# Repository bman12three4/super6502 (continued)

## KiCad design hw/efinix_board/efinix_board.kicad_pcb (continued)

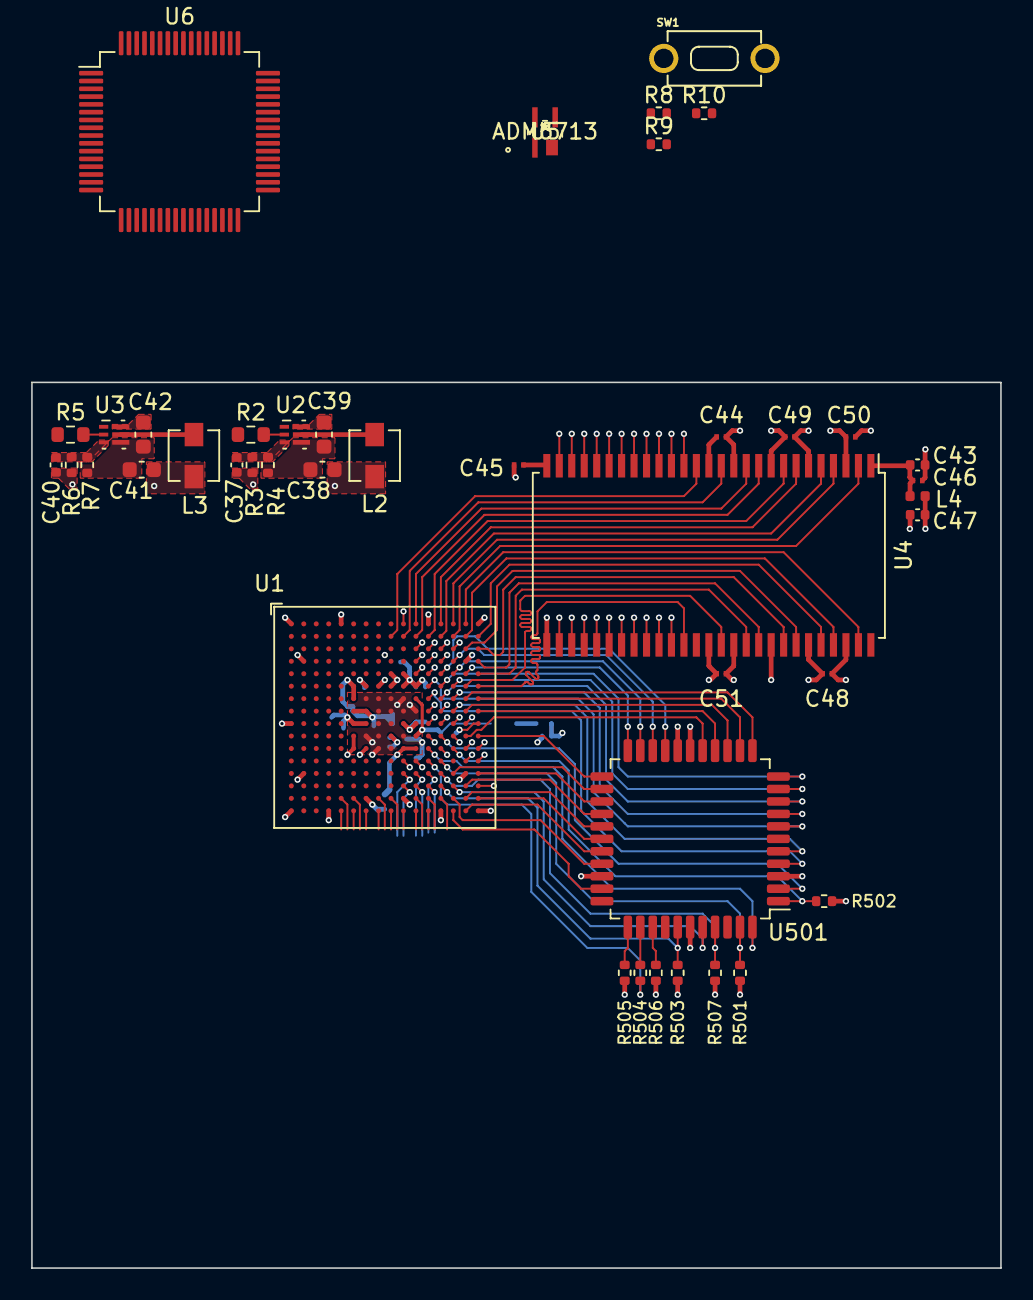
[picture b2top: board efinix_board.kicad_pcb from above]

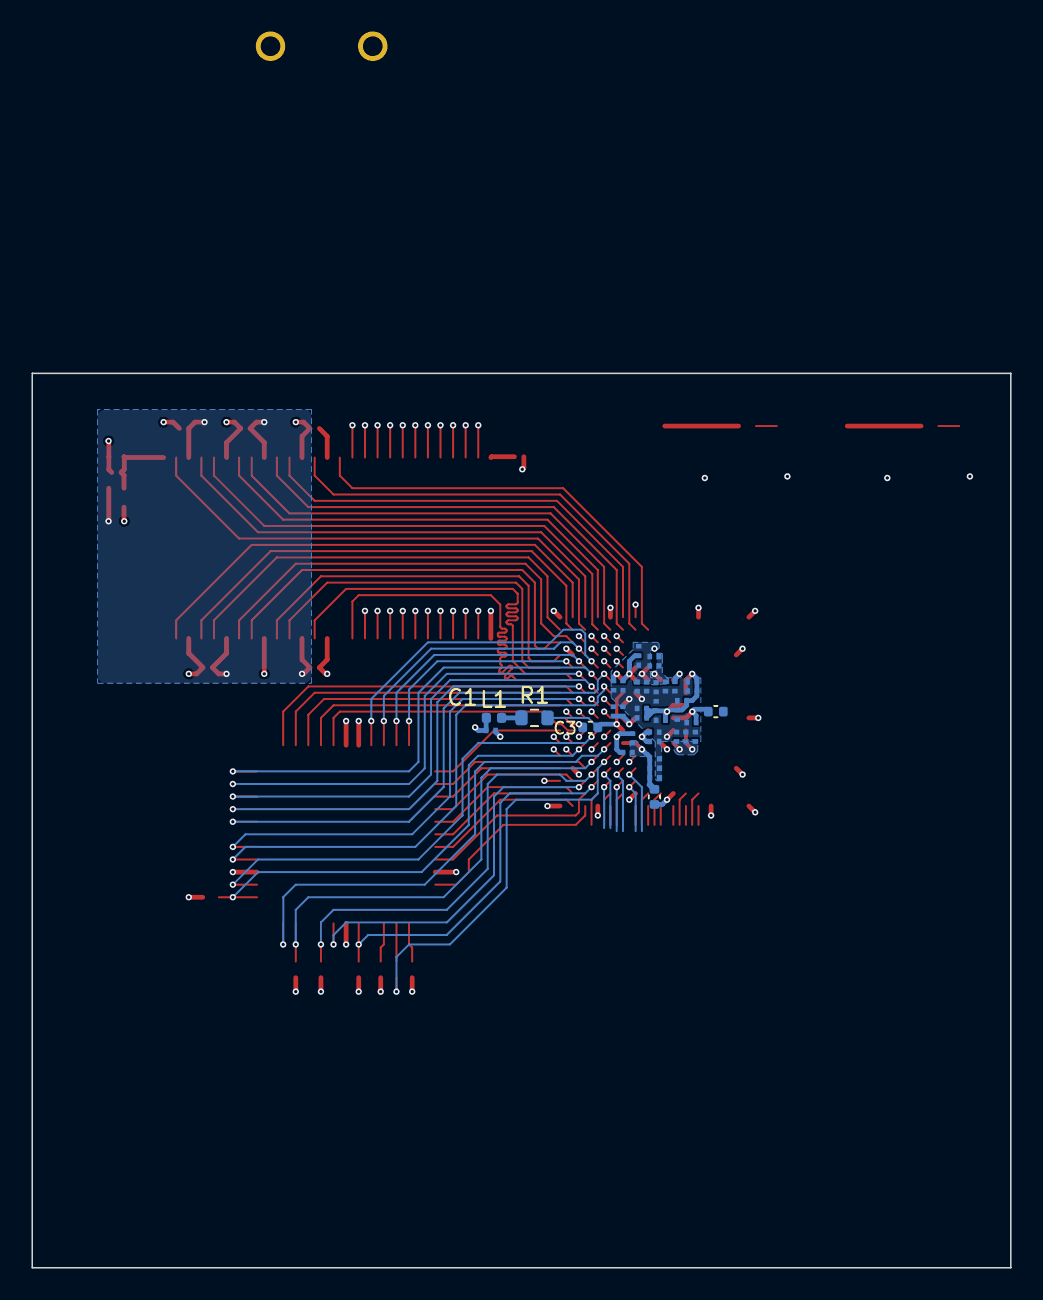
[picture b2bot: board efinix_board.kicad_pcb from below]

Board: 6 copper layers, 62.2 x 56.9 mm, 80 parts (38 on the bottom side), 92 nets.

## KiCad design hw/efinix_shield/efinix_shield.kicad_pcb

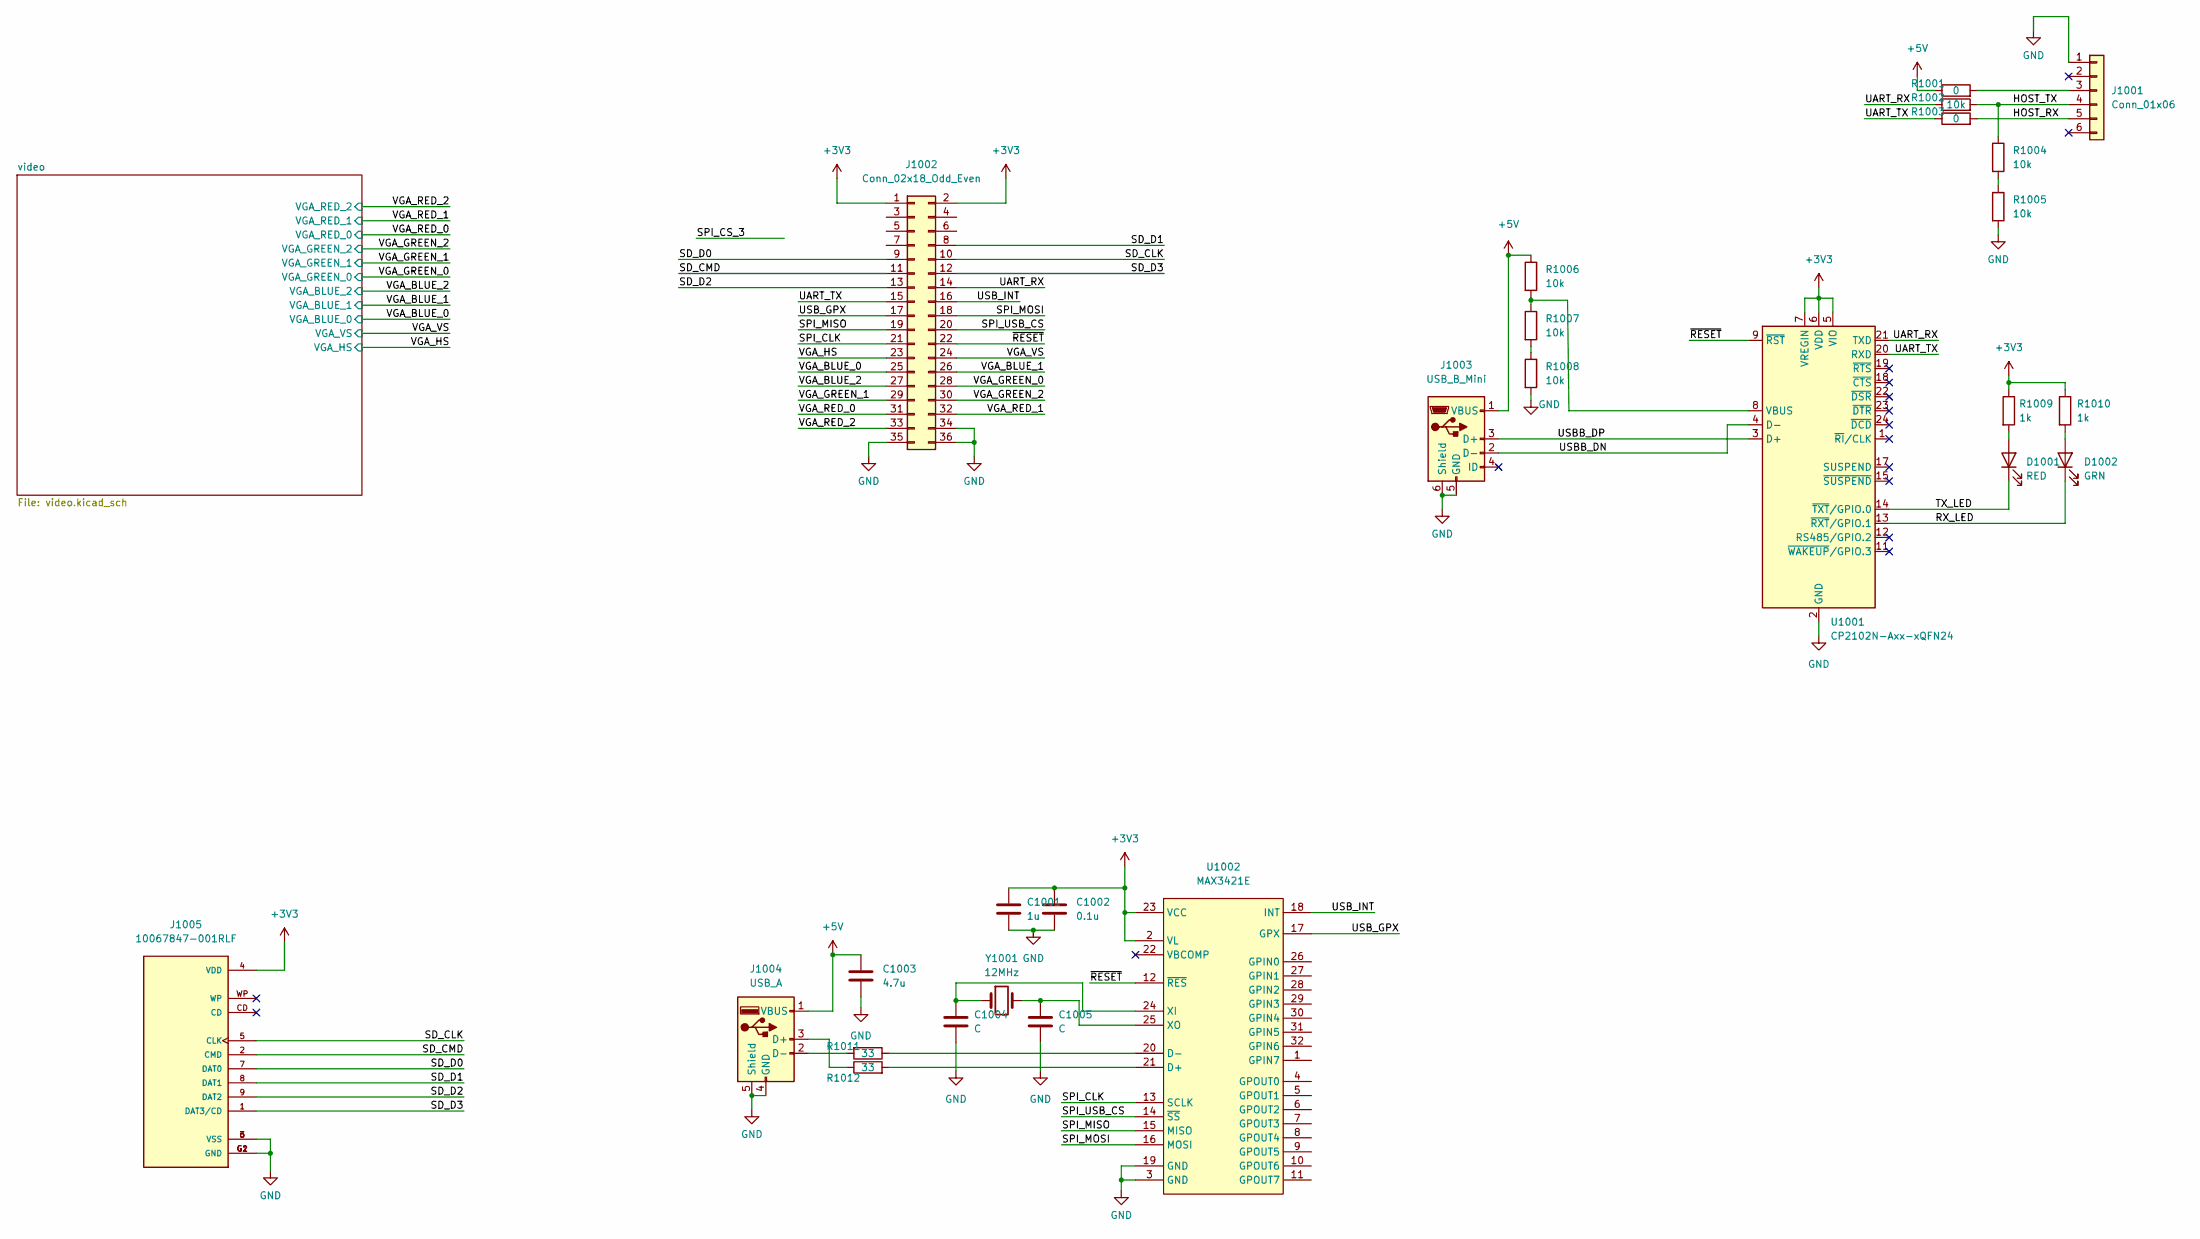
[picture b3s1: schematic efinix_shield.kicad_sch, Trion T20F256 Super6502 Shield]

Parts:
C1001: 1u; C_0805_2012Metric_Pad1.18x1.45mm_HandSolder
C1002: 0.1u; C_0805_2012Metric_Pad1.18x1.45mm_HandSolder
C1003: 4.7u; C_0805_2012Metric_Pad1.18x1.45mm_HandSolder
C1004, C1005: C; C_0805_2012Metric_Pad1.18x1.45mm_HandSolder
D1001: RED; LED_0805_2012Metric_Pad1.15x1.40mm_HandSolder
D1002: GRN; LED_0805_2012Metric_Pad1.15x1.40mm_HandSolder
J1001: Conn_01x06; PinHeader_1x06_P2.54mm_Vertical
J1002: Conn_02x18_Odd_Even; PinSocket_2x18_P2.54mm_Vertical
J1003: USB_B_Mini; USB_Mini-B_Wuerth_65100516121_Horizontal
J1004: USB_A; FCI_87520-0010BLF
J1005: 10067847-001RLF; AMPHENOL_10067847-001RLF; PARTREV K
R1001, R1003: 0; R_0805_2012Metric_Pad1.20x1.40mm_HandSolder
R1002, R1004, R1005, R1006, R1007, R1008: 10k; R_0805_2012Metric_Pad1.20x1.40mm_HandSolder
R1009, R1010: 1k; R_0805_2012Metric_Pad1.20x1.40mm_HandSolder
R1011, R1012: 33; R_0805_2012Metric_Pad1.20x1.40mm_HandSolder
U1001: CP2102N-Axx-xQFN24; QFN-24-1EP_4x4mm_P0.5mm_EP2.6x2.6mm
U1002: MAX3421E; LQFP-32_5x5mm_P0.5mm
Y1001: 12MHz; Crystal_HC49-U_Vertical

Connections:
+3V3: C1001.1, C1002.1, J1002.1, J1002.2, J1005.4 (VDD), R1009.1, R1010.1, U1001.5 (VIO), U1001.6 (VDD), U1001.7 (VREGIN), U1002.2 (VL), U1002.23 (VCC)
+5V: C1003.1, J1003.1 (VBUS), J1004.1 (VBUS), R1001.1, R1006.1
/HOST_RX: J1001.5, R1003.2
/HOST_TX: J1001.4, R1002.2, R1004.1
/RX_LED: D1002.1 (K), U1001.13 (~RXT/GPIO.1)
/SD_CLK: J1002.10, J1005.5 (CLK)
/SD_CMD: J1002.11, J1005.2 (CMD)
/SD_D0: J1002.9, J1005.7 (DAT0)
/SD_D1: J1002.8, J1005.8 (DAT1)
/SD_D2: J1002.13, J1005.9 (DAT2)
/SD_D3: J1002.12, J1005.1 (DAT3/CD)
/SPI_CLK: J1002.21, U1002.13 (SCLK)
/SPI_MISO: J1002.19, U1002.15 (MISO)
/SPI_MOSI: J1002.18, U1002.16 (MOSI)
/SPI_USB_CS: J1002.20, U1002.14 (~SS)
/TX_LED: D1001.1 (K), U1001.14 (~TXT/GPIO.0)
/UART_RX: J1002.14, R1002.1, U1001.21 (TXD)
/UART_TX: J1002.15, R1003.1, U1001.20 (RXD)
/USBB_DN: J1003.2 (D-), U1001.4 (D-)
/USBB_DP: J1003.3 (D+), U1001.3 (D+)
/USB_GPX: J1002.17, U1002.17 (GPX)
/USB_INT: J1002.16, U1002.18 (INT)
/VGA_BLUE_0: J1002.25; also elsewhere on the board
/VGA_BLUE_1: J1002.26; also elsewhere on the board
/VGA_BLUE_2: J1002.27; also elsewhere on the board
/VGA_GREEN_0: J1002.28; also elsewhere on the board
/VGA_GREEN_1: J1002.29; also elsewhere on the board
/VGA_GREEN_2: J1002.30; also elsewhere on the board
/VGA_HS: J1002.23; also elsewhere on the board
/VGA_RED_0: J1002.31; also elsewhere on the board
/VGA_RED_1: J1002.32; also elsewhere on the board
/VGA_RED_2: J1002.33; also elsewhere on the board
/VGA_VS: J1002.24; also elsewhere on the board
/~RESET: J1002.22, U1001.9 (~RST), U1002.12 (~RES)
GND: C1001.2, C1002.2, C1003.2, C1004.2, C1005.2, J1001.1, J1002.34, J1002.35, J1002.36, J1003.5 (GND), J1003.6 (Shield), J1004.4 (GND), J1004.5 (Shield), J1005.3 (VSS), J1005.6 (VSS), J1005.G1 (GND), J1005.G2 (GND), R1005.2, R1008.2, U1001.2 (GND), U1001.25 (GND), U1002.3 (GND), U1002.19 (GND); also elsewhere on the board
unnamed: C1004.1, U1002.24 (XI), Y1001.1
unnamed: C1005.1, U1002.25 (XO), Y1001.2
unnamed: D1001.2 (A), R1009.2
unnamed: D1002.2 (A), R1010.2
unnamed: J1001.3, R1001.2
unnamed: J1004.2 (D-), R1011.2
unnamed: J1004.3 (D+), R1012.1
unnamed: R1004.2, R1005.1
unnamed: R1006.2, R1007.1, U1001.8 (VBUS)
unnamed: R1007.2, R1008.1
unnamed: R1011.1, U1002.20 (D-)
unnamed: R1012.2, U1002.21 (D+)

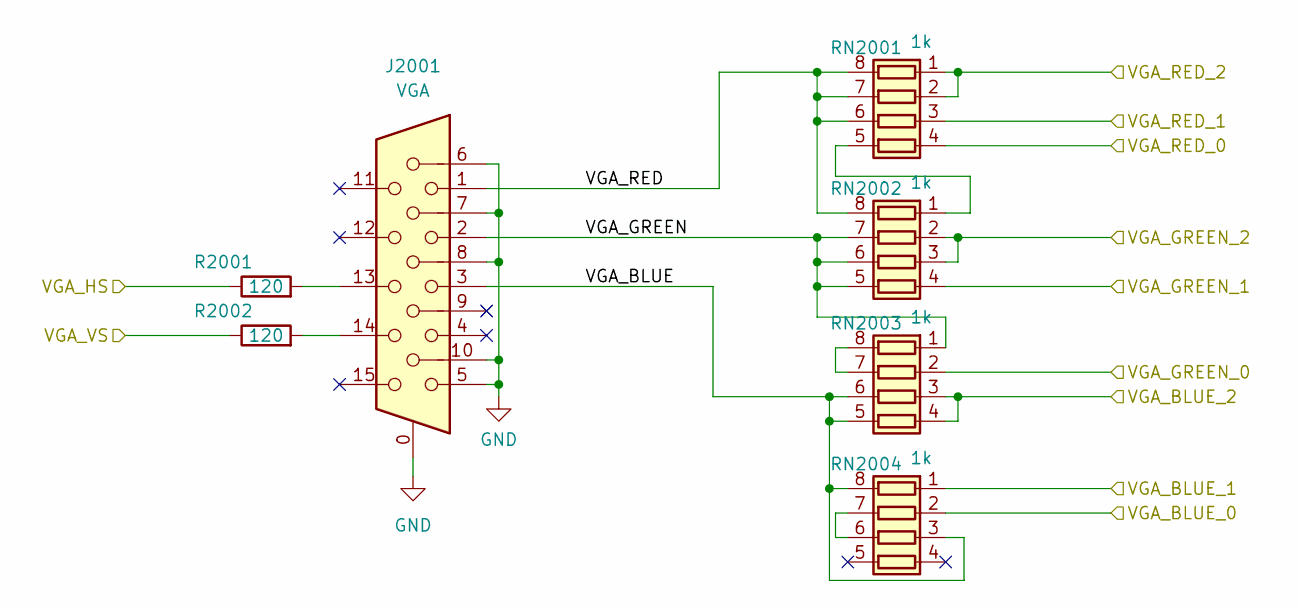
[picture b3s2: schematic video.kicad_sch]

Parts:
J2001: VGA; ICD15S13E4GX00LF; Part Name ICD15S13E4GX00LF
R2001, R2002: 120; R_0805_2012Metric_Pad1.20x1.40mm_HandSolder
RN2001, RN2002, RN2003, RN2004: 1k; R_Array_Concave_4x0402

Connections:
/VGA_BLUE_0: RN2004.2 (R2.1); also elsewhere on the board
/VGA_BLUE_1: RN2004.1 (R1.1); also elsewhere on the board
/VGA_BLUE_2: RN2003.3 (R3.1), RN2003.4 (R4.1); also elsewhere on the board
/VGA_GREEN_0: RN2003.2 (R2.1); also elsewhere on the board
/VGA_GREEN_1: RN2002.4 (R4.1); also elsewhere on the board
/VGA_GREEN_2: RN2002.2 (R2.1), RN2002.3 (R3.1); also elsewhere on the board
/VGA_HS: R2001.1; also elsewhere on the board
/VGA_RED_0: RN2001.4 (R4.1); also elsewhere on the board
/VGA_RED_1: RN2001.3 (R3.1); also elsewhere on the board
/VGA_RED_2: RN2001.1 (R1.1), RN2001.2 (R2.1); also elsewhere on the board
/VGA_VS: R2002.1; also elsewhere on the board
/video/VGA_BLUE: J2001.3, RN2003.5 (R4.2), RN2003.6 (R3.2), RN2004.3 (R3.1), RN2004.8 (R1.2)
/video/VGA_GREEN: J2001.2, RN2002.5 (R4.2), RN2002.6 (R3.2), RN2002.7 (R2.2), RN2003.1 (R1.1)
/video/VGA_RED: J2001.1, RN2001.6 (R3.2), RN2001.7 (R2.2), RN2001.8 (R1.2), RN2002.8 (R1.2)
GND: J2001.0, J2001.5, J2001.6, J2001.7, J2001.8, J2001.10; also elsewhere on the board
unnamed: J2001.13, R2001.2
unnamed: J2001.14, R2002.2
unnamed: RN2001.5 (R4.2), RN2002.1 (R1.1)
unnamed: RN2003.7 (R2.2), RN2003.8 (R1.2)
unnamed: RN2004.6 (R3.2), RN2004.7 (R2.2)

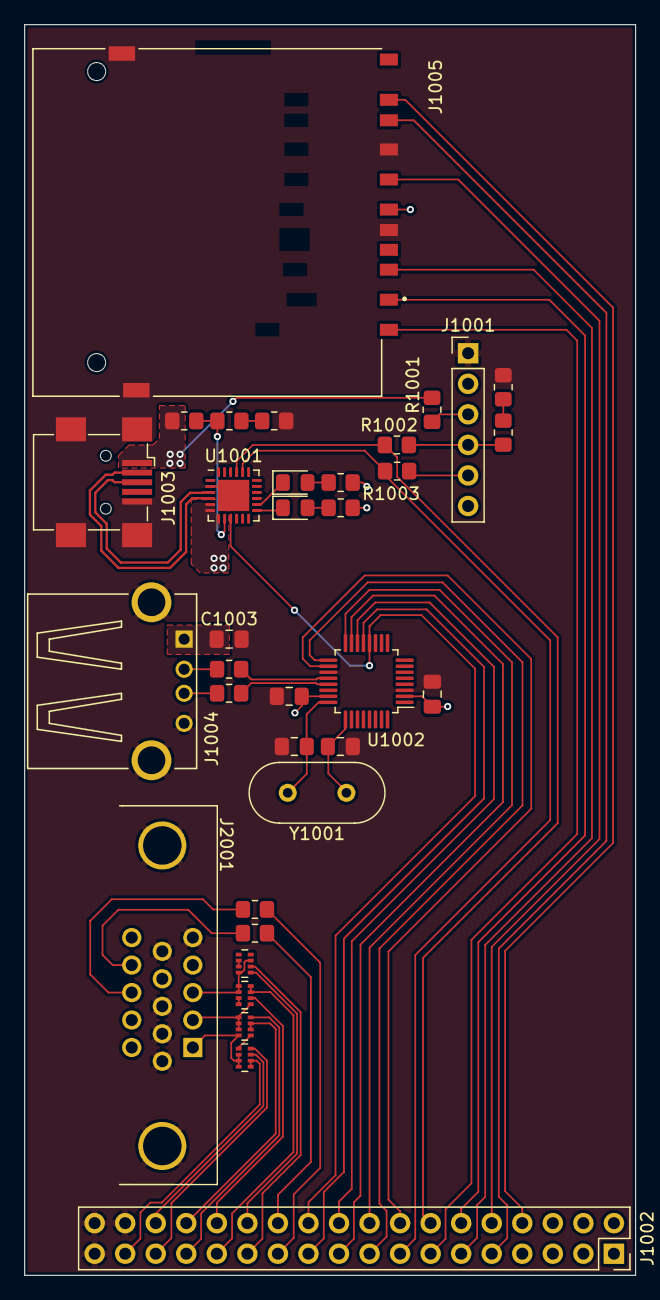
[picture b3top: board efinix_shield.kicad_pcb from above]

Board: 2 copper layers, 50.8 x 104.0 mm, 34 parts (0 on the bottom side), 55 nets.

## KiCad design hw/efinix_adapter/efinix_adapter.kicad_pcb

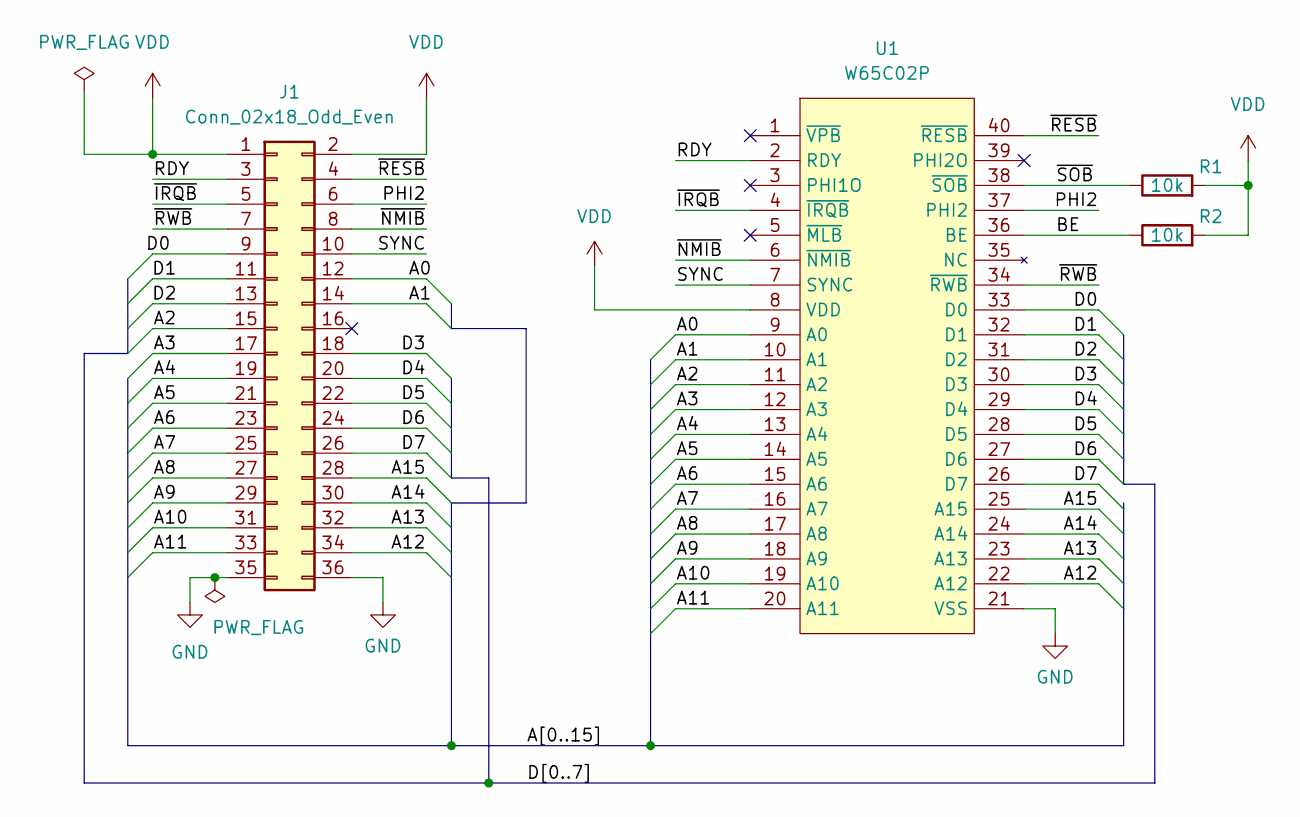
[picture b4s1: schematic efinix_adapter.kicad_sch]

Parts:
J1: Conn_02x18_Odd_Even; PinSocket_2x18_P2.54mm_Vertical
R1, R2: 10k; R_0603_1608Metric_Pad0.98x0.95mm_HandSolder
U1: W65C02P; DIP-40_W15.24mm_Socket_LongPads

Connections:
/A0: J1.12, U1.9 (A0)
/A1: J1.14, U1.10 (A1)
/A2: J1.15, U1.11 (A2)
/A3: J1.17, U1.12 (A3)
/A4: J1.19, U1.13 (A4)
/A5: J1.21, U1.14 (A5)
/A6: J1.23, U1.15 (A6)
/A7: J1.25, U1.16 (A7)
/A8: J1.27, U1.17 (A8)
/A9: J1.29, U1.18 (A9)
/A10: J1.31, U1.19 (A10)
/A11: J1.33, U1.20 (A11)
/A12: J1.34, U1.22 (A12)
/A13: J1.32, U1.23 (A13)
/A14: J1.30, U1.24 (A14)
/A15: J1.28, U1.25 (A15)
/BE: R2.1, U1.36 (BE)
/D0: J1.9, U1.33 (D0)
/D1: J1.11, U1.32 (D1)
/D2: J1.13, U1.31 (D2)
/D3: J1.18, U1.30 (D3)
/D4: J1.20, U1.29 (D4)
/D5: J1.22, U1.28 (D5)
/D6: J1.24, U1.27 (D6)
/D7: J1.26, U1.26 (D7)
/PHI2: J1.6, U1.37 (PHI2)
/RDY: J1.3, U1.2 (RDY)
/SYNC: J1.10, U1.7 (SYNC)
/~IRQB: J1.5, U1.4 (~IRQB)
/~NMIB: J1.8, U1.6 (~NMIB)
/~RESB: J1.4, U1.40 (~RESB)
/~RWB: J1.7, U1.34 (~RWB)
/~SOB: R1.1, U1.38 (~SOB)
GND: J1.35, J1.36, U1.21 (VSS)
VDD: J1.1, J1.2, R1.2, R2.2, U1.8 (VDD)

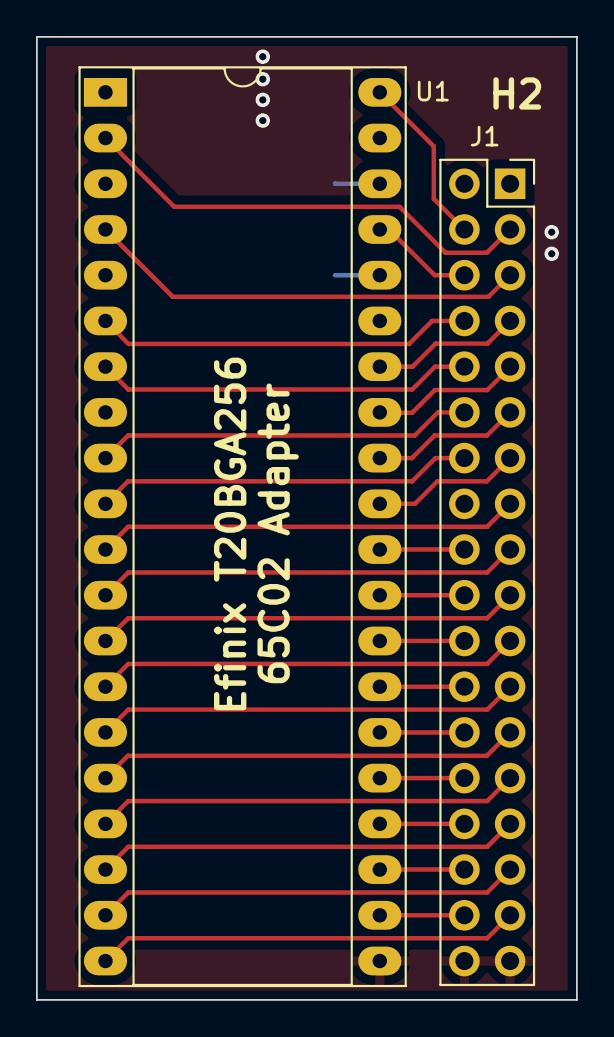
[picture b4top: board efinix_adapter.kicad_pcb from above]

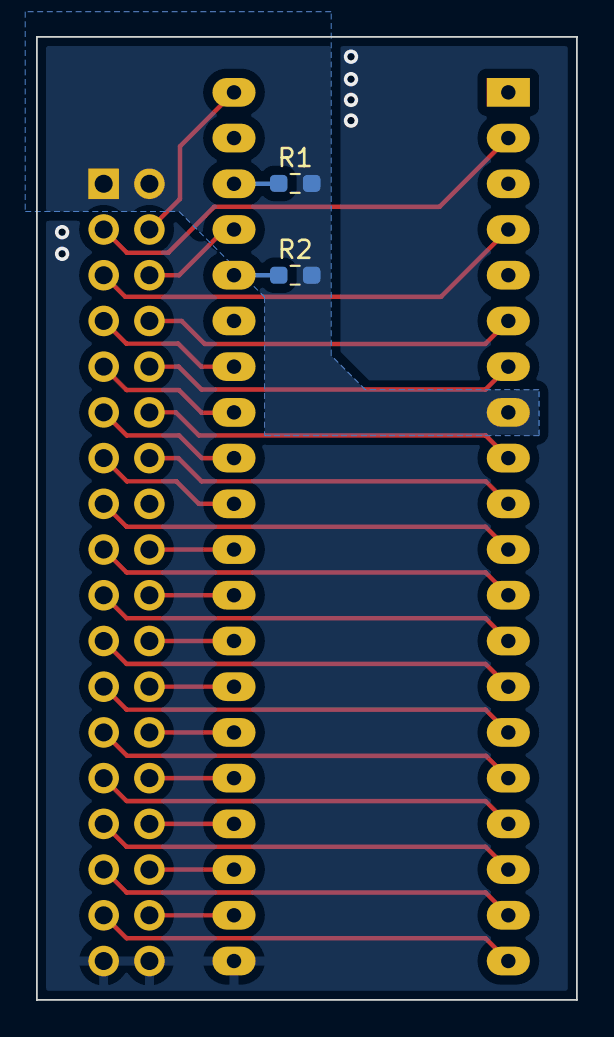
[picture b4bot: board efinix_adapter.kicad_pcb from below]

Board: 2 copper layers, 30.0 x 53.5 mm, 4 parts (2 on the bottom side), 35 nets.

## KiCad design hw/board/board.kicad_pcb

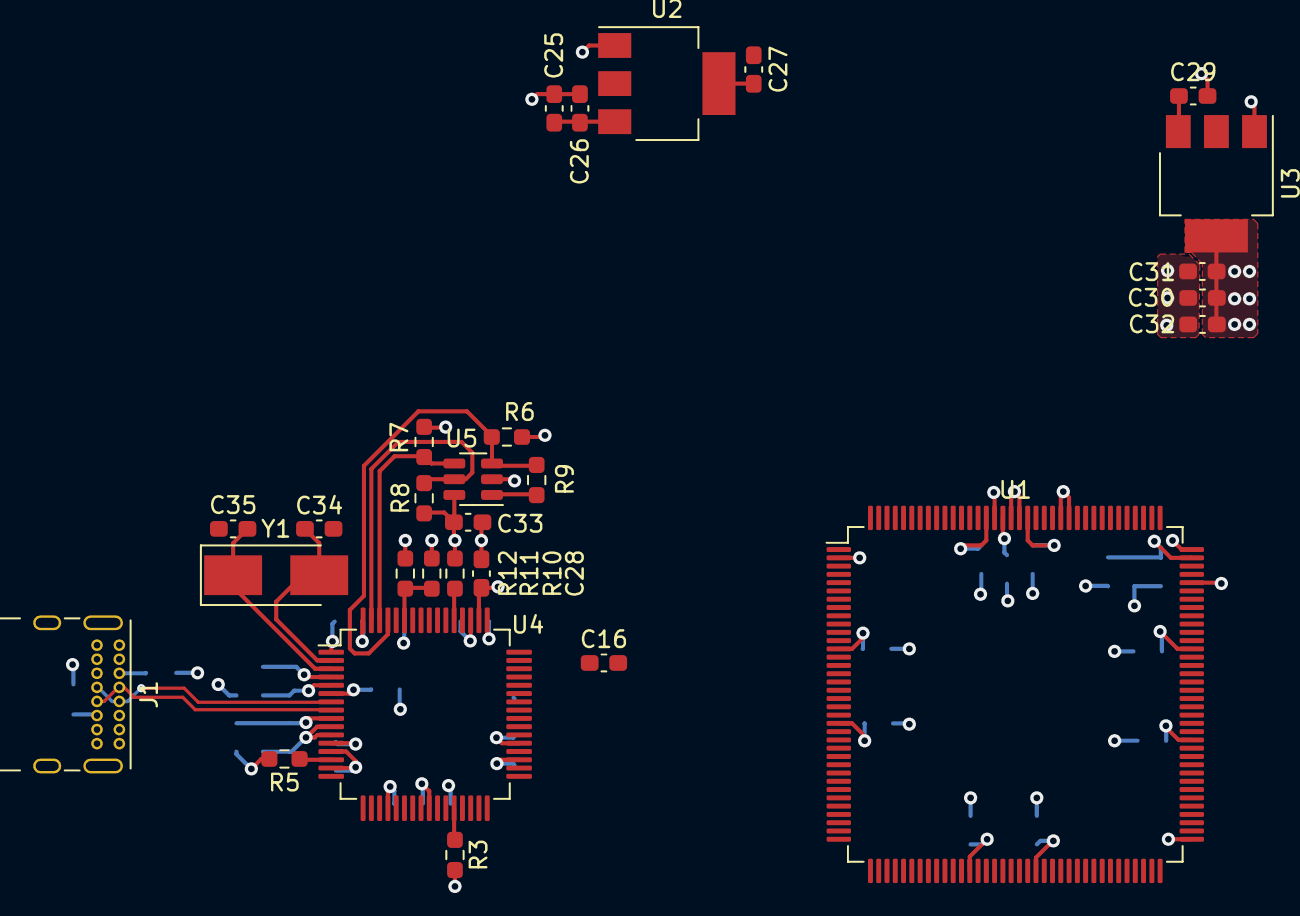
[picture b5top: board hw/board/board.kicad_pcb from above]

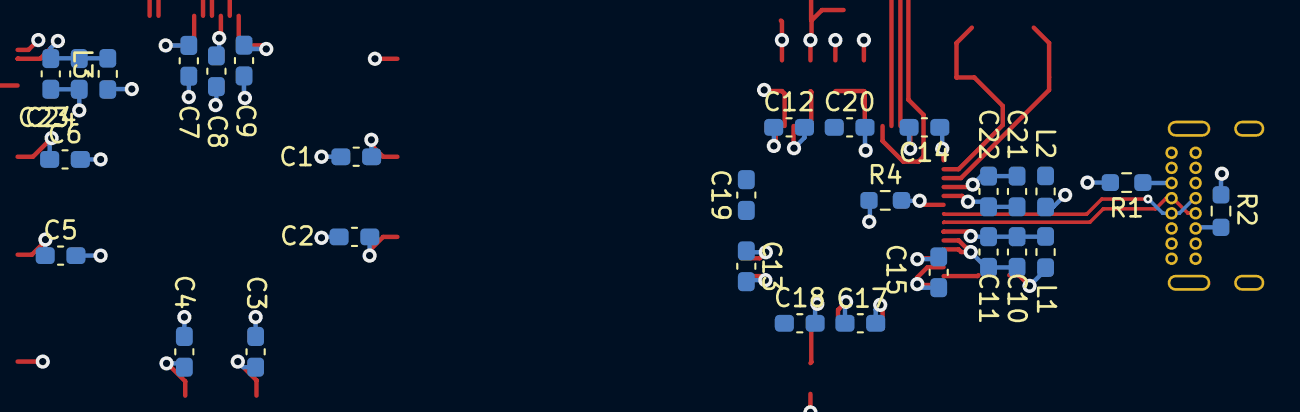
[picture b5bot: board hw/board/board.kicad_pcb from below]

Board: 4 copper layers, 57 parts (29 on the bottom side), 23 nets.

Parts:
C1, C2, C3, C4, C5, C6, C7, C8, C9, C11, C13, C14, C15, C17, C18, C19, C20, C22, C31: 100n; C_0603_1608Metric_Pad1.08x0.95mm_HandSolder
C10, C12, C16, C21, C23, C28: 4.7u; C_0603_1608Metric_Pad1.08x0.95mm_HandSolder
C24, C33: 0.1u; C_0603_1608Metric_Pad1.08x0.95mm_HandSolder
C25: 10u; C_0603_1608Metric_Pad1.08x0.95mm_HandSolder
C26, C30: 1u; C_0603_1608Metric_Pad1.08x0.95mm_HandSolder
C27, C32: 10n; C_0603_1608Metric_Pad1.08x0.95mm_HandSolder
C29: 2.2u; C_0603_1608Metric_Pad1.08x0.95mm_HandSolder
C34, C35: LOAD; C_0603_1608Metric_Pad1.08x0.95mm_HandSolder
J1: USB_C_Receptacle_USB2.0; USB_C_Receptacle_GCT_USB4085
L1, L2, L3: 600R @ 100MHz; L_0603_1608Metric_Pad1.05x0.95mm_HandSolder
R1, R2: 5.1k; R_0603_1608Metric_Pad0.98x0.95mm_HandSolder
R3, R6, R7, R8, R10, R12: 10k; R_0603_1608Metric_Pad0.98x0.95mm_HandSolder
R4: 12k 1%; R_0603_1608Metric_Pad0.98x0.95mm_HandSolder
R5: R; R_0603_1608Metric_Pad0.98x0.95mm_HandSolder
R9: 2.2k; R_0603_1608Metric_Pad0.98x0.95mm_HandSolder
R11: 4.7k; R_0603_1608Metric_Pad0.98x0.95mm_HandSolder
U1: T8Q144; LQFP-144_20x20mm_P0.5mm
U2: LD1117S33TR_SOT223; SOT-223-3_TabPin2
U3: LD1117S12TR_SOT223; SOT-223-3_TabPin2
U4: FT2232HL; LQFP-64_10x10mm_P0.5mm
U5: 93LCxxBxxOT; SOT-23-6
Y1: 12MHz; Crystal_SMD_5032-2Pin_5.0x3.2mm_HandSoldering

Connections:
+1V2: C1.1, C2.1, C3.1, C4.1, C5.1, C6.1, C7.1, C8.1, C9.1, C30.1, C31.1, C32.1, L3.1, U1.13 (VCC), U1.22 (VCC), U1.49 (VCC), U1.57 (VCC), U1.85 (VCC), U1.96 (VCC), U1.125 (VCC), U1.128 (VCC), U1.130 (VCC), U3.2 (VO)
+3V3: C16.1, C17.1, C18.1, C19.1, C20.1, C27.1, C28.1, C29.1, C33.1, L1.1, L2.1, R3.2, R5.2, R6.1, R7.1, R8.1, R10.2, U1.12 (VCCIO_1C_1D), U1.21 (VCCIO_1B), U1.23 (VCCIO_1A), U1.51 (VCCIO_4B), U1.52 (VCCIO_4B), U1.62 (VCCIO_4A), U1.63 (VCCIO_4A), U1.88 (VCCIO_3E), U1.91 (VCCIO_3D), U1.95 (VCCIO_3B_3C), U1.122 (VCCIO_3A), U1.143 (VCCIO_1E), U2.2 (VO), U3.3 (VI), U4.20 (VCCIO), U4.31 (VCCIO), U4.42 (VCCIO), U4.50 (VREGIN), U4.56 (VCCIO), U5.6 (VCC)
+5V: C25.1, C26.1, J1.A4 (VBUS), J1.A9 (VBUS), J1.B4 (VBUS), J1.B9 (VBUS), R11.2, U2.3 (VI)
/FT_RST: R5.1, U4.14 (~RESET)
/USB_N: J1.A7 (D-), J1.B7 (D-), U4.7 (DM)
/USB_P: J1.A6 (D+), J1.B6 (D+), U4.8 (DP)
/VPHY: C21.1, C22.1, L2.2, U4.4 (VPHY)
/VPLL: C10.1, C11.1, L1.2, U4.9 (VPLL)
/VRO: C12.1, C13.1, C14.1, C15.1, U4.12 (VCORE), U4.37 (VCORE), U4.49 (VREGOUT), U4.64 (VCORE)
GND: C1.2, C2.2, C3.2, C4.2, C5.2, C6.2, C7.2, C8.2, C9.2, C10.2, C11.2, C12.2, C13.2, C14.2, C15.2, C16.2, C17.2, C18.2, C19.2, C20.2, C21.2, C22.2, C23.2, C24.2, C25.2, C26.2, C27.2, C28.2, C29.2, C30.2, C31.2, C32.2, C33.2, C34.1, C35.1, J1.A1 (GND), J1.A12 (GND), J1.B1 (GND), J1.B12 (GND), J1.S1 (SHIELD), R1.2, R2.2, R4.1, R12.2, U1.1 (GND), U1.5 (GND), U1.9 (GND), U1.37 (GND), U1.44 (GND), U1.50 (GND), U1.64 (GND), U1.94 (GND), U1.104 (GND), U1.108 (GND), U1.120 (GND), U1.121 (GND), U1.126 (GND), U1.127 (GND), U1.129 (GND), U1.133 (GND), U2.1 (GND), U3.1 (GND), U4.1 (GND), U4.5 (GND), U4.10 (AGND), U4.11 (GND), U4.13 (TEST), U4.15 (GND), U4.25 (GND), U4.35 (GND), U4.47 (GND), U4.51 (GND), U5.2 (GND)
unnamed: C23.1, C24.1, L3.2, U1.2 (VCCA_TL), U1.73 (VCCA_BR), U1.107 (VCCA_TR)
unnamed: C34.2, U4.2 (OSCI), Y1.2
unnamed: C35.2, U4.3 (OSCO), Y1.1
unnamed: J1.A5 (CC1), R1.1
unnamed: J1.B5 (CC2), R2.1
unnamed: R3.1, U4.28 (ACBUS2)
unnamed: R4.2, U4.6 (REF)
unnamed: R6.2, R9.2, U4.61 (EEDATA), U5.3 (DI)
unnamed: R7.2, U4.62 (EECLK), U5.4 (CLK)
unnamed: R8.2, U4.63 (EECS), U5.5 (CS)
unnamed: R9.1, U5.1 (DO)
unnamed: R10.1, U4.53 (BCBUS2)
unnamed: R11.1, R12.1, U4.59 (BCBUS7)

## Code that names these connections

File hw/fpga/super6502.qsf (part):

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set_global_assignment -name PARTITION_FITTER_PRESERVATION_LEVEL PLACEMENT_AND_ROUTING -section_id Top
set_global_assignment -name PARTITION_COLOR 16764057 -section_id Top
set_location_assignment PIN_V10 -to cpu_led
set_location_assignment PIN_W10 -to cpu_vpb
set_location_assignment PIN_V9 -to cpu_resb
set_location_assignment PIN_W9 -to cpu_rdy
set_location_assignment PIN_V8 -to cpu_sob
set_location_assignment PIN_V7 -to cpu_phi2
set_location_assignment PIN_W6 -to cpu_be
set_location_assignment PIN_W5 -to cpu_rwb
set_location_assignment PIN_AA14 -to cpu_data[0]
set_location_assignment PIN_W12 -to cpu_data[1]
set_location_assignment PIN_AB12 -to cpu_data[2]
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set_location_assignment PIN_Y11 -to cpu_addr[2]
set_location_assignment PIN_AB13 -to cpu_addr[1]
set_location_assignment PIN_W13 -to cpu_addr[0]
set_location_assignment PIN_AA15 -to cpu_sync
set_location_assignment PIN_V5 -to cpu_nmib
set_location_assignment PIN_W7 -to cpu_mlb
set_location_assignment PIN_W8 -to cpu_irqb
set_location_assignment PIN_C17 -to HEX0[6]
set_location_assignment PIN_D17 -to HEX0[5]
set_location_assignment PIN_E16 -to HEX0[4]
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set_global_assignment -name POWER_PRESET_COOLING_SOLUTION "23 MM HEAT SINK WITH 200 LFPM AIRFLOW"
set_global_assignment -name POWER_BOARD_THERMAL_MODEL "NONE (CONSERVATIVE)"
set_location_assignment PIN_B8 -to rst_n
set_location_assignment PIN_P11 -to clk_50
set_global_assignment -name ENABLE_OCT_DONE OFF
set_global_assignment -name EXTERNAL_FLASH_FALLBACK_ADDRESS 00000000
set_global_assignment -name USE_CONFIGURATION_DEVICE OFF
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
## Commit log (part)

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2023-08-01 remote testing code
2023-08-07 Get bios calls starting to work
2023-08-09 Link bootloader with bios to get access to symbols
    By doing this we don't need to call bios functions, we can just jsr
    directly to the addresses. This does mean that everytime the bios
    changes the bootloader has to change, but ideally all the bootloader
    does is load the bios and then get remapped out of memory. Any important
    drivers like file system can be loaded from the bootloader.
    This also means that the runtime functions are located in the bios for
2023-08-09 Modify disk script to leave partition table intact
2023-08-12 Restart kernel
2023-08-12 Update cc65
2023-08-13 Find bootloader in FAT
2023-08-13 Remove some debug info
2023-08-15 Load a multi-sector file and execute it
2023-08-15 Automatically copy rom image and warn about rebuild
2023-08-16 Add comments and use less magic
2023-08-22 Find kernel in second stage bootloader
2023-08-23 Update order for kernel segments
2023-08-23 start o65dump.py
2023-08-23 Update o65dump to show reloc and undef symbols
2023-08-24 Factor out relocation code into method
2023-08-24 Use old offset calculation, save ptr3
    Looks like cprintf modifies ptr3, so make sure to save it if you are
    calling that.
    There also may have been an issue with how the previous sector address
    was calculated, the one which does not account for carries seems to
    work.
2023-08-24 Don't save segments as separate files
2023-08-26 Start reading options
2023-08-26 Read entire file into memory
2023-08-26 Get super simple kernel code running
2023-08-26 Disable inits which fail
2023-08-26 Kernel crashing
2023-08-26 Fix incorrect stack start
2023-09-02 Fix zerobss bug
    Well, not really fix but problem is avoided for now
2023-09-04 Copy bios device functions to kernel
2023-09-07 Add null mapper
2023-09-08 Add diagram, throw some code together
2023-09-19 Organize Project
2023-09-19 Move mapper into src folder
2023-09-19 Add sim cpu
2023-09-22 update sim environment
2023-09-22 Get something simulated
    Infinite loop being caused somewhere
2023-09-23 remove sim submodule
2023-09-23 Add submodule back
2023-09-24 Add memory
2023-09-24 Add support for test programs
2023-09-24 Change sdrclk and sysclk to have aligned rising edges
2023-09-26 Up the sim time
2023-09-26 Gate rdy behind sdram_cs #28
2023-09-27 Update verilog-6502 bslathi19/verilog-6502@aaf4c084ef68b9ee1646dc5acc982820868e090f
2023-09-28 Disable sdr debug, initialize uart status
2023-09-28 Fix uart status multiple drivers
2023-09-28 Remove unneeded CR
2023-09-29 Revert "Update .gitlab-ci.yml file"
    This reverts commit 3e79267ae701b666d5271477f4f3fabb4306021a
2023-09-29 Try a bad commit
2023-09-29 remove env call
2023-09-29 Add build sim to ci
2023-09-29 add build cc65 to steps
2023-09-29 recursive submodule
2023-09-29 Resolve "Add build check to CI"
2023-09-29 Add sd emulator as submodule
2023-09-30 Remove toolchan from sim step
2023-09-30 Add lib to artifacts
2023-09-30 fix typo
2023-09-30 Resolve "Use dependencies instead of makefile chaining"
2023-09-30 Add dependencies on test code for running sim
2023-09-30 Update init.env to check for EFX_SETUP
2023-09-30 Specify correct artifact
2023-09-30 Refactor makefile, update verilog-sd-emulator
2023-10-01 Don't have sd wait in simulation
    need to figure out how to set that RTL_SIM flag only when we are
    compiling code for the sim
    also bro the sim is like 8000x slower than irl.
2023-10-05 Update sd, remove wait state
2023-10-05 Remove another wait, update sd emulator
2023-10-05 Increase sim time to get into sd block reads
2023-10-06 Add script for creating verilog filesystem image
2023-10-06 Update verilog sd
2023-10-06 Use REPO_TOP in script, call script from makefile
2023-10-07 remove sd from regular sim
    Figure out how to do this later
2023-10-11 Increase sim time, update verilog sd
2023-10-11 full sim requires toolchain
2023-10-11 Use repo based path for creating fs image
2023-10-15 Fix sdram wrapper state machine
2023-10-15 Add jsr test
2023-10-15 Fix synthesis issue
2023-10-16 rework state machine
2023-10-16 Update build
2023-10-16 Revert super6502 back to before mapper
2023-10-17 Add Docs
2023-10-17 Add mapper and testbench
2023-10-18 Update testbench, fix off by 1
2023-10-20 Route all addresses through mapper
2023-10-20 Refactor for FPGA synthesis
2023-10-21 Update C test to actually use mapper a little bit
2023-10-22 Add code testbench
2023-10-22 Update to use new binary sd card image
2023-10-24 Try long test
2023-10-26 Change boot2 to use new offsets as well
2023-10-26 Fix off by 1 error
2023-10-26 run vvp unbuffered
2023-10-27 Reduce sim time
2023-10-27 Make kernel as part of full chip sim
2023-10-27 Up sim time
2023-10-28 Update kernel makefile, test more kernel code
2023-10-29 Skip the copydata in kernel setup
2023-10-30 Fix off by 1 in o65 option decoding
2023-10-31 Add first design
2023-11-01 Second diagram
2023-11-01 Add beginnings of interrupt controller
2023-11-15 Add skeleton of interrupt controller
2023-11-16 Fix makefile, fix how interrupts are triggered
2023-11-16 Fix level triggered test, add to ci
2023-11-17 Test interrupt priority
2023-11-18 Implement RTC
2023-11-18 Check all edge interrupts
2023-11-18 Add toolchain dependency to sim
2023-11-19 Add LICENSE
2023-11-19 Add README
2023-11-19 Add rtc code test
2023-11-19 Update RTC code test
2023-11-19 Fix irq code tb now that interrupts are used
2023-11-19 Toolchain: Reduce jobs, add retries
2023-11-20 Add pic docs
2023-11-20 Init rtc and pic in kernel
2023-11-20 PIC: Disable all irqs at start
2023-11-21 Fix bad sp and writing to zp0
2023-11-21 Enable interrupts, print out current rtc tick
2023-11-21 add interrupt init code (and increase rtc tick rate)
2023-11-21 Clear interrupt before waiting
2023-11-21 #53 Reduce interrupts to 128
2023-11-22 add uart interrupt
2023-11-22 Update irq test code
2023-11-22 Add init_hex.mem to artifacts for fpga build
2023-11-22 update devices_setup_test makefile
2023-11-22 try needs
2023-11-23 Add init code for mapper
    init_mapper now remaps so that it can change irq vectors
2023-11-23 Add toolchain dependency to full sim
2023-11-23 Decouple spi_clk from cpu_clk
2023-11-23 Move fast signals to fast reset
2023-11-25 Reduce cpu speed
2023-11-26 Add parts list
2023-11-26 Don't clone kicad library for ci
2023-11-26 Add updated kicad library
2023-11-27 Create schematic heirarchy
2023-11-28 Start work on ddr
2023-11-28 Use new kicad library without 3d models
2023-11-29 Add quick uart irq test
2023-11-29 Add serial driver and irq support
2023-11-29 Start terminal driver
2023-11-29 First shot at terminal read
2023-12-01 Add some flops to the mapper
    This is NOT how to do CDC
2023-12-01 add really ugly
2023-12-01 Fix more bugs
2023-12-01 Change kicad library commit
    Needs to be a commit in kicad-library-2
2023-12-02 Use tmp1 instead of y register
    popa clobbers y
2023-12-03 Add dumb multiplier code test
2023-12-04 Update cc65 pointer with PVSeek
2023-12-05 Calculate data start
2023-12-05 Add some basic code, build kernel stuff in tree
2023-12-05 Look through files without trying too hard
2023-12-05 Read out very long file, but not very long name
2023-12-06 Get something working with read
    It is not reading offset correctly
2023-12-06 Get read working a little bit more. Need to handle edge cases!
2023-12-07 Add close, add filesystem code to main kernel for hardware testing
2023-12-08 Try clearing carry flag, that always helps. Also don't need verilog image anymore
2023-12-09 Add fixes for multiple sectors per cluster
2023-12-10 Add basic syscall docs
2023-12-11 Throw some stuff up
2023-12-12 #73 First go at relocating interrupt code
2024-03-03 Add basic project with cpu, ram and rom
2024-03-03 Add basic ci and separate hw from all target
2024-03-03 Fix PLL settings, add cpu output clock
2024-03-03 Add test code and top level Makefile
2024-03-03 Make a venv in build
2024-03-03 Build software correctly, ignore debugger files
2024-03-04 Add sdram, don't think it works though
2024-03-04 Fix sdram sim
    Just need to add the RTL_SIM define
2024-03-04 Add sd controller submodule
2024-03-10 Update rtl common and sd controller submodules
2024-03-10 Do synthesis with sd controller
2024-03-10 Add sd io pins
2024-03-10 Require python3.11
2024-03-11 Add program target to makefiles
2024-03-13 Update sd controller and test code
2024-03-13 Update sd controller for sim
2024-03-13 Add sd emulator (need to add sd mode)
2024-03-14 Run simulation with verilog sd emulator
    This also slowed the cpu clock down, we should speed it up again
2024-03-15 Update rtl common since I commited to the wrong branch
2024-03-15 Update verilog sd to get up to cmd7
2024-03-16 Update submodules, update sources
2024-03-31 Remove axi_crossbar, add wb2axip
2024-04-01 Use new axi xbar
2024-04-01 Synthesize with new xbar
2024-07-15 Remove old SD controller
2024-07-16 Add sd and wb2axi submodules
2024-07-16 Also load iverilog module
2024-07-16 Move controller and make wrapper folder
2024-07-17 First pass at integrating sd controller
2024-07-17 Reset renaming, set card_detect
2024-07-18 Update rtl-common, fix some axi violations in cpu writes
2024-07-18 Add new sd wrapper
    Wrapper is neccesary for the address offset and also because the
    controller will trigger on reads/writes to registers, but we need access
    to each byte of the 32 bit registers.
    The wrapper will need to somehow chose when to actually trigger the
    controller, maybe by having shadow registers?
2024-07-21 switch to zipcpu sd sim
2024-07-21 Move shadow to us, get some commands going
2024-07-22 Update SD version and start working on DMA
2024-07-22 Start working on axi dma
2024-07-27 Add wait for DMA (should poll bit instead)
2024-07-27 Add new DMA files to project config
2024-08-01 Fix sdspi, add missing source file
2024-08-01 Update sdspi with merged version
2024-08-02 Fix shadow regs, fix tristate buffer (add pullup)
2024-08-06 Add start of tcp docs
2024-08-16 Update network_processor docs
2024-08-16 Add start of regs
2024-08-18 Use sram instead of sdram in sim, fully switch to verilator
2024-08-18 Add ntw files to project
2024-08-19 Move tcp into its own wrapper
2024-08-20 Add verilog ethernet
2024-08-20 Update drawing again
2024-08-20 Update diagrams again (2)
2024-08-20 Update regs
2024-08-20 Update diagrams again (4)
2024-08-20 Update diagrams again (5)
2024-08-20 Changes for synthesis
2024-08-20 Pass synthesis
2024-08-21 Add new stream dma git repo
2024-08-21 Add blank stubs.list
2024-08-21 Separate ip streams
2024-08-21 Add basic m2s code
2024-08-30 Change from ddr buffers to regular fifos
2024-08-30 Remove mux/demus from dma
2024-09-02 Remove sub from verilog-ethernet
2024-09-02 Uncomment module load
    oops
2024-09-02 update reg addr width, add fifo for m2s dma to write to
2024-09-03 Update so I can switch computers
2024-09-03 Update test, use scapy
2024-09-03 Send basic header
2024-09-03 Send ARP response, not request
2024-09-08 Add up dest parser
2024-09-09 Add basic acking to synacking
2024-09-10 Move to 4 TCP units for synthesis
    Otherwise it does not fit in the T20
2024-09-10 Add mii clocks to constraints
2024-09-13 Make a pcapng file, not pcap
2024-09-13 Hack length in
2024-09-14 Add TCP calculator
2024-09-14 Add checksum calc to fpga sources
2024-09-22 Add ntw sim to ci
2024-09-22 Use scapy to send real packets
2024-09-23 Try to recieve data
    I think we need to actually do checksum for data
2024-09-23 Remove recv call
    need to wait until checksum i presume
2024-09-24 add kicad library back
2024-09-24 Add project, t120f484
2024-09-24 Do some work on clocks
2024-09-28 add fin
2024-10-14 Get some fin support
2024-10-14 Big update to try and pass timing. reduces tcp streams to 1
2024-10-14 Increase TCP count to 2
    After removing all the inferred latches, we have enough space to have 2
    TCP streams instead of just 1. Also we have way more timing slack.
    Lesson learned, inferred latches are *really* bad and you should remove
    them first before anything else.
2024-10-15 Increase seq when sending fins
